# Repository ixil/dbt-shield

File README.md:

# dbt-shield
Shield: Pellet extrusion controller for ABB robotic arms w/ profinet I/O

Mini-shield: Filament extrusion controller for UR arms, to be used in the MAS ETH DFAB

## Shield
---

### Specs
---
16bit 24V digital Input\
8bit 24v digital Output\
4bit 0-10v analog Input\
4x 500mW MOSFETS\
4x SSR 240VAC 2A\
2x K-Type Thermocouple amplifiers

## Mini-Shield

### Specs
---
4bit 24V digital Input\
2x TMC2130 Stepper Driver\
2x 100W MOSFETS\
3x 500mW MOSFETS\
1x 104NT thermistor

[Pin-Out / Set-Up / Connections](https://github.com/hiiragii/dbt-shield/tree/master/mini)

### UR5 FDM  

UR 5 e3d Titan Aero + Super Volcano mounting bracket
[stl / step files](https://github.com/hiiragii/dbt-shield/tree/master/ur5aero)

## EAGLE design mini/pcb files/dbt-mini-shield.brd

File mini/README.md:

## Pinout
---

The 2x16 pin terminal blocks on the right side are directly connected to the respective arduino pin (eg D0 on the terminal block is digital pin 0 on the arduino).

## Connections
---
+ Connect the 24v power supply wires to the top terminal.
+ Connect the Extruder optional object fan to OUT0 and OUT1.
+ Connect the thermistor leads to TH0+ and TH0-, polarity doesn't matter.
+ Connect the super-volcano heater to OUT3 and GND (first 2 pins on the terminal block).
+ Connect the first stepper coil to M1.1A and M1.1B. Connect the second coil to M1.2A and M1.2B. Polarity doesn't matter, you can reverse the direction of rotation directly in software or by swapping 2 leads of the same coil (eg. M1.1A and M1.1B).  
+ Connect the 5 lead cable to the 4-bit input terminal block, where IN.b3 is the MSB.

## Set-up
---

## Digital-Input

In.b0 = heater enable, active LOW
In.b1 = stepper enable, active LOW
In.b2 = speed 
In.b3 = speed 

speed(5mm/s)  01
speed(15mm/s) 10
speed(30mm/s) 11

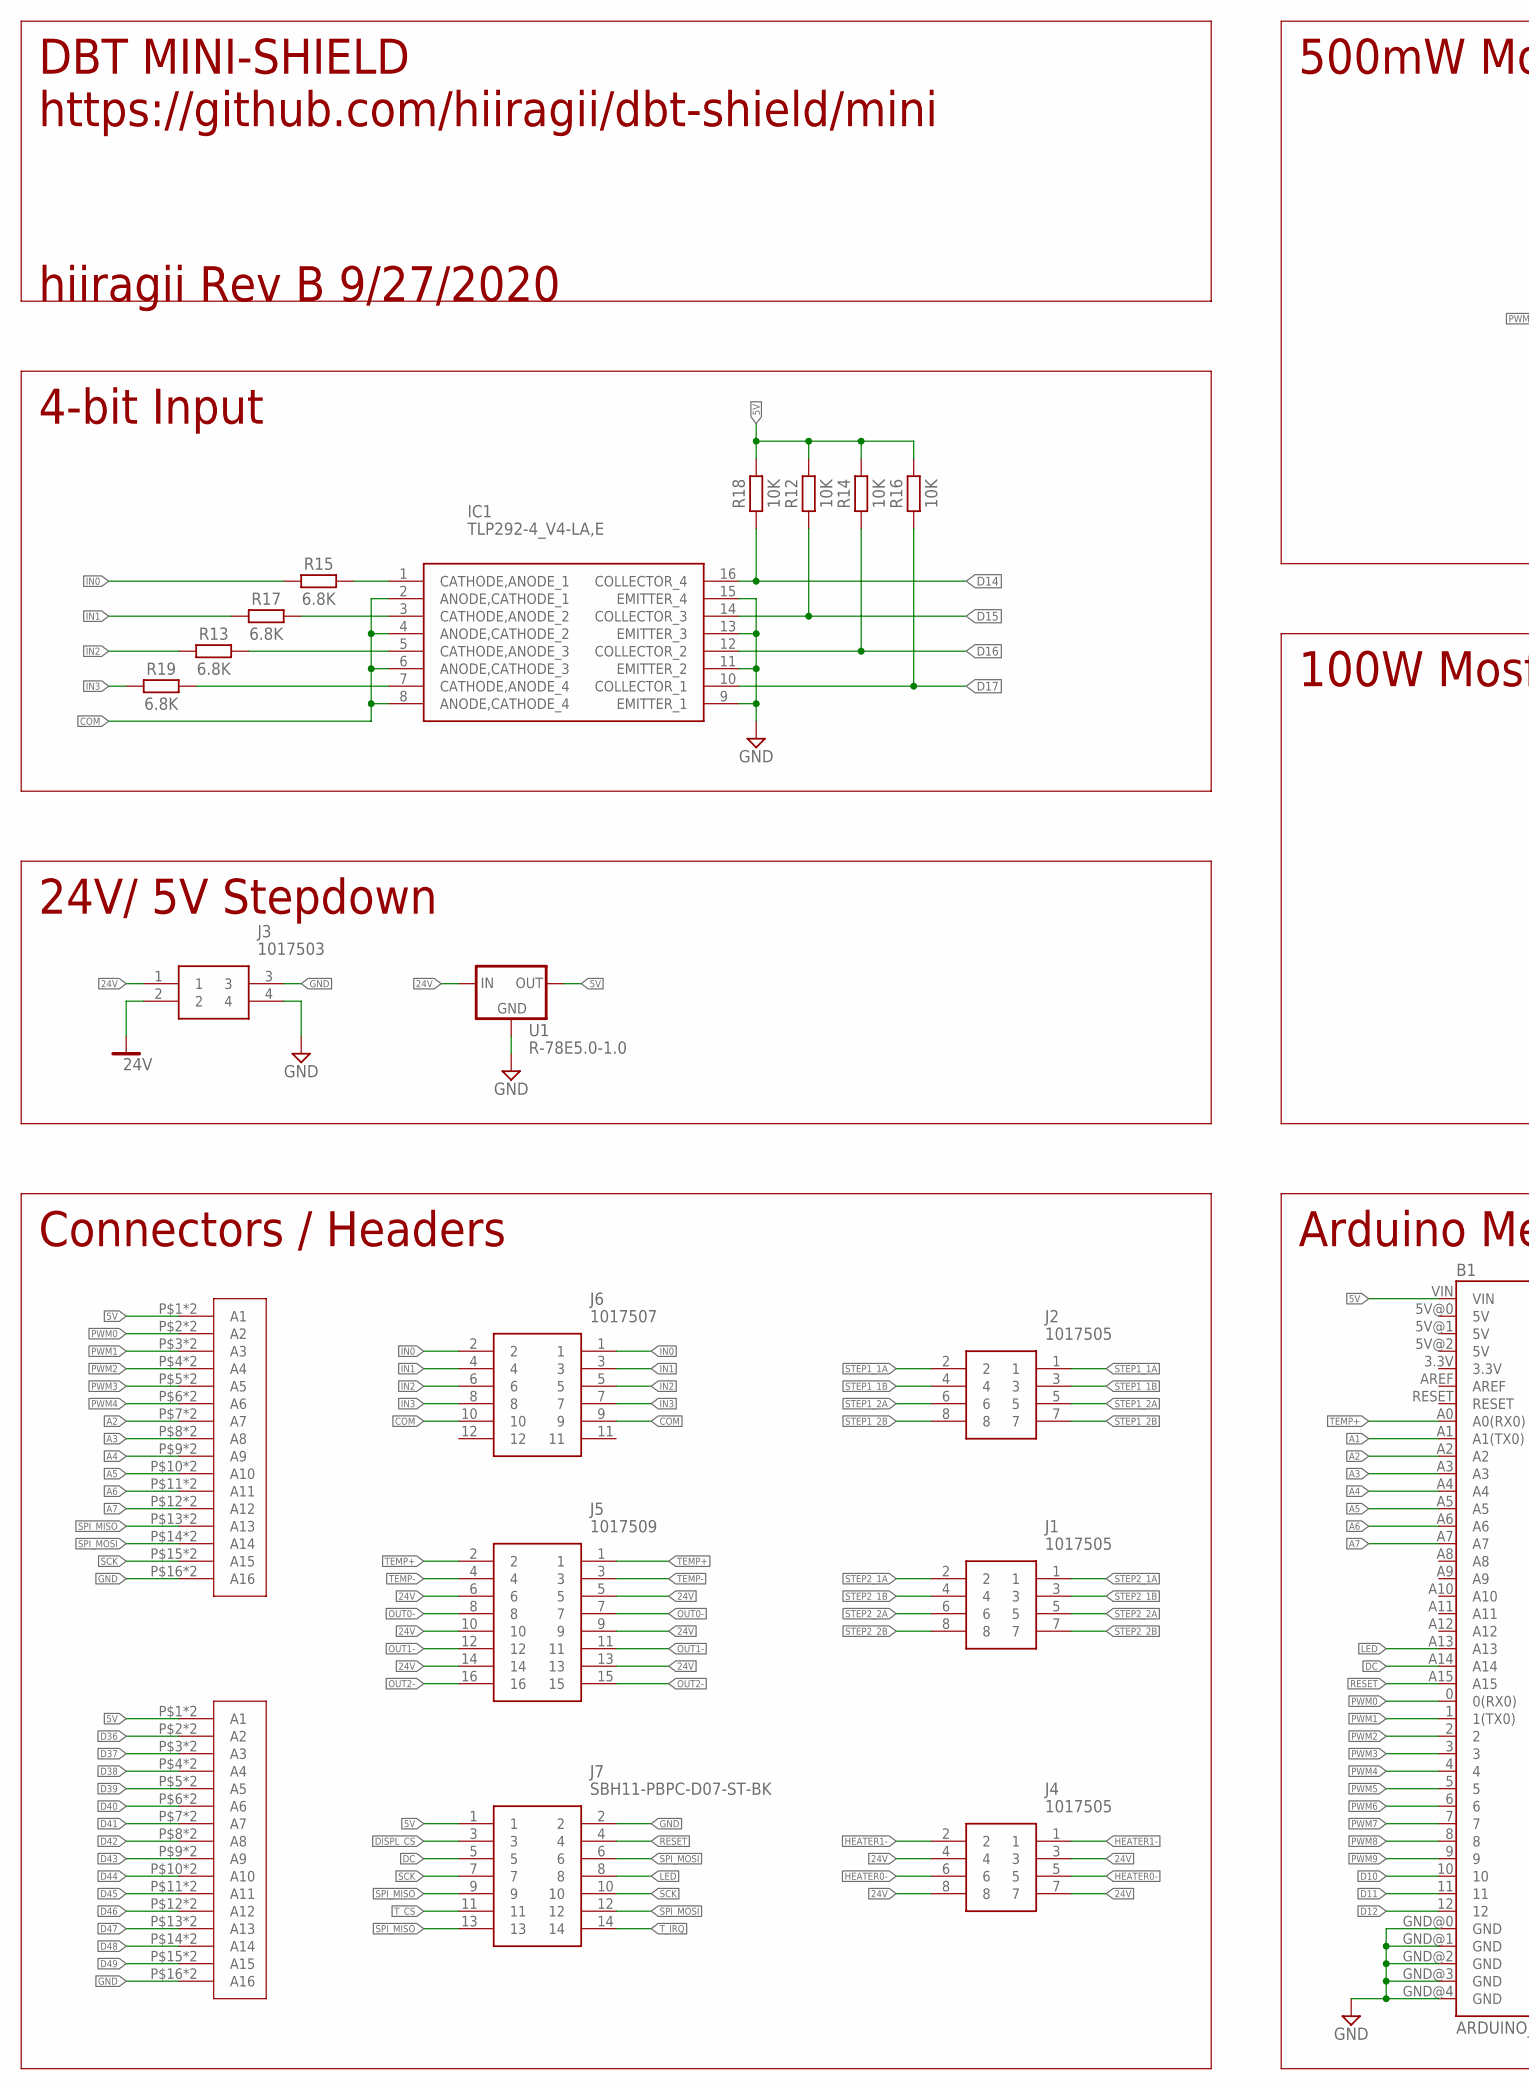
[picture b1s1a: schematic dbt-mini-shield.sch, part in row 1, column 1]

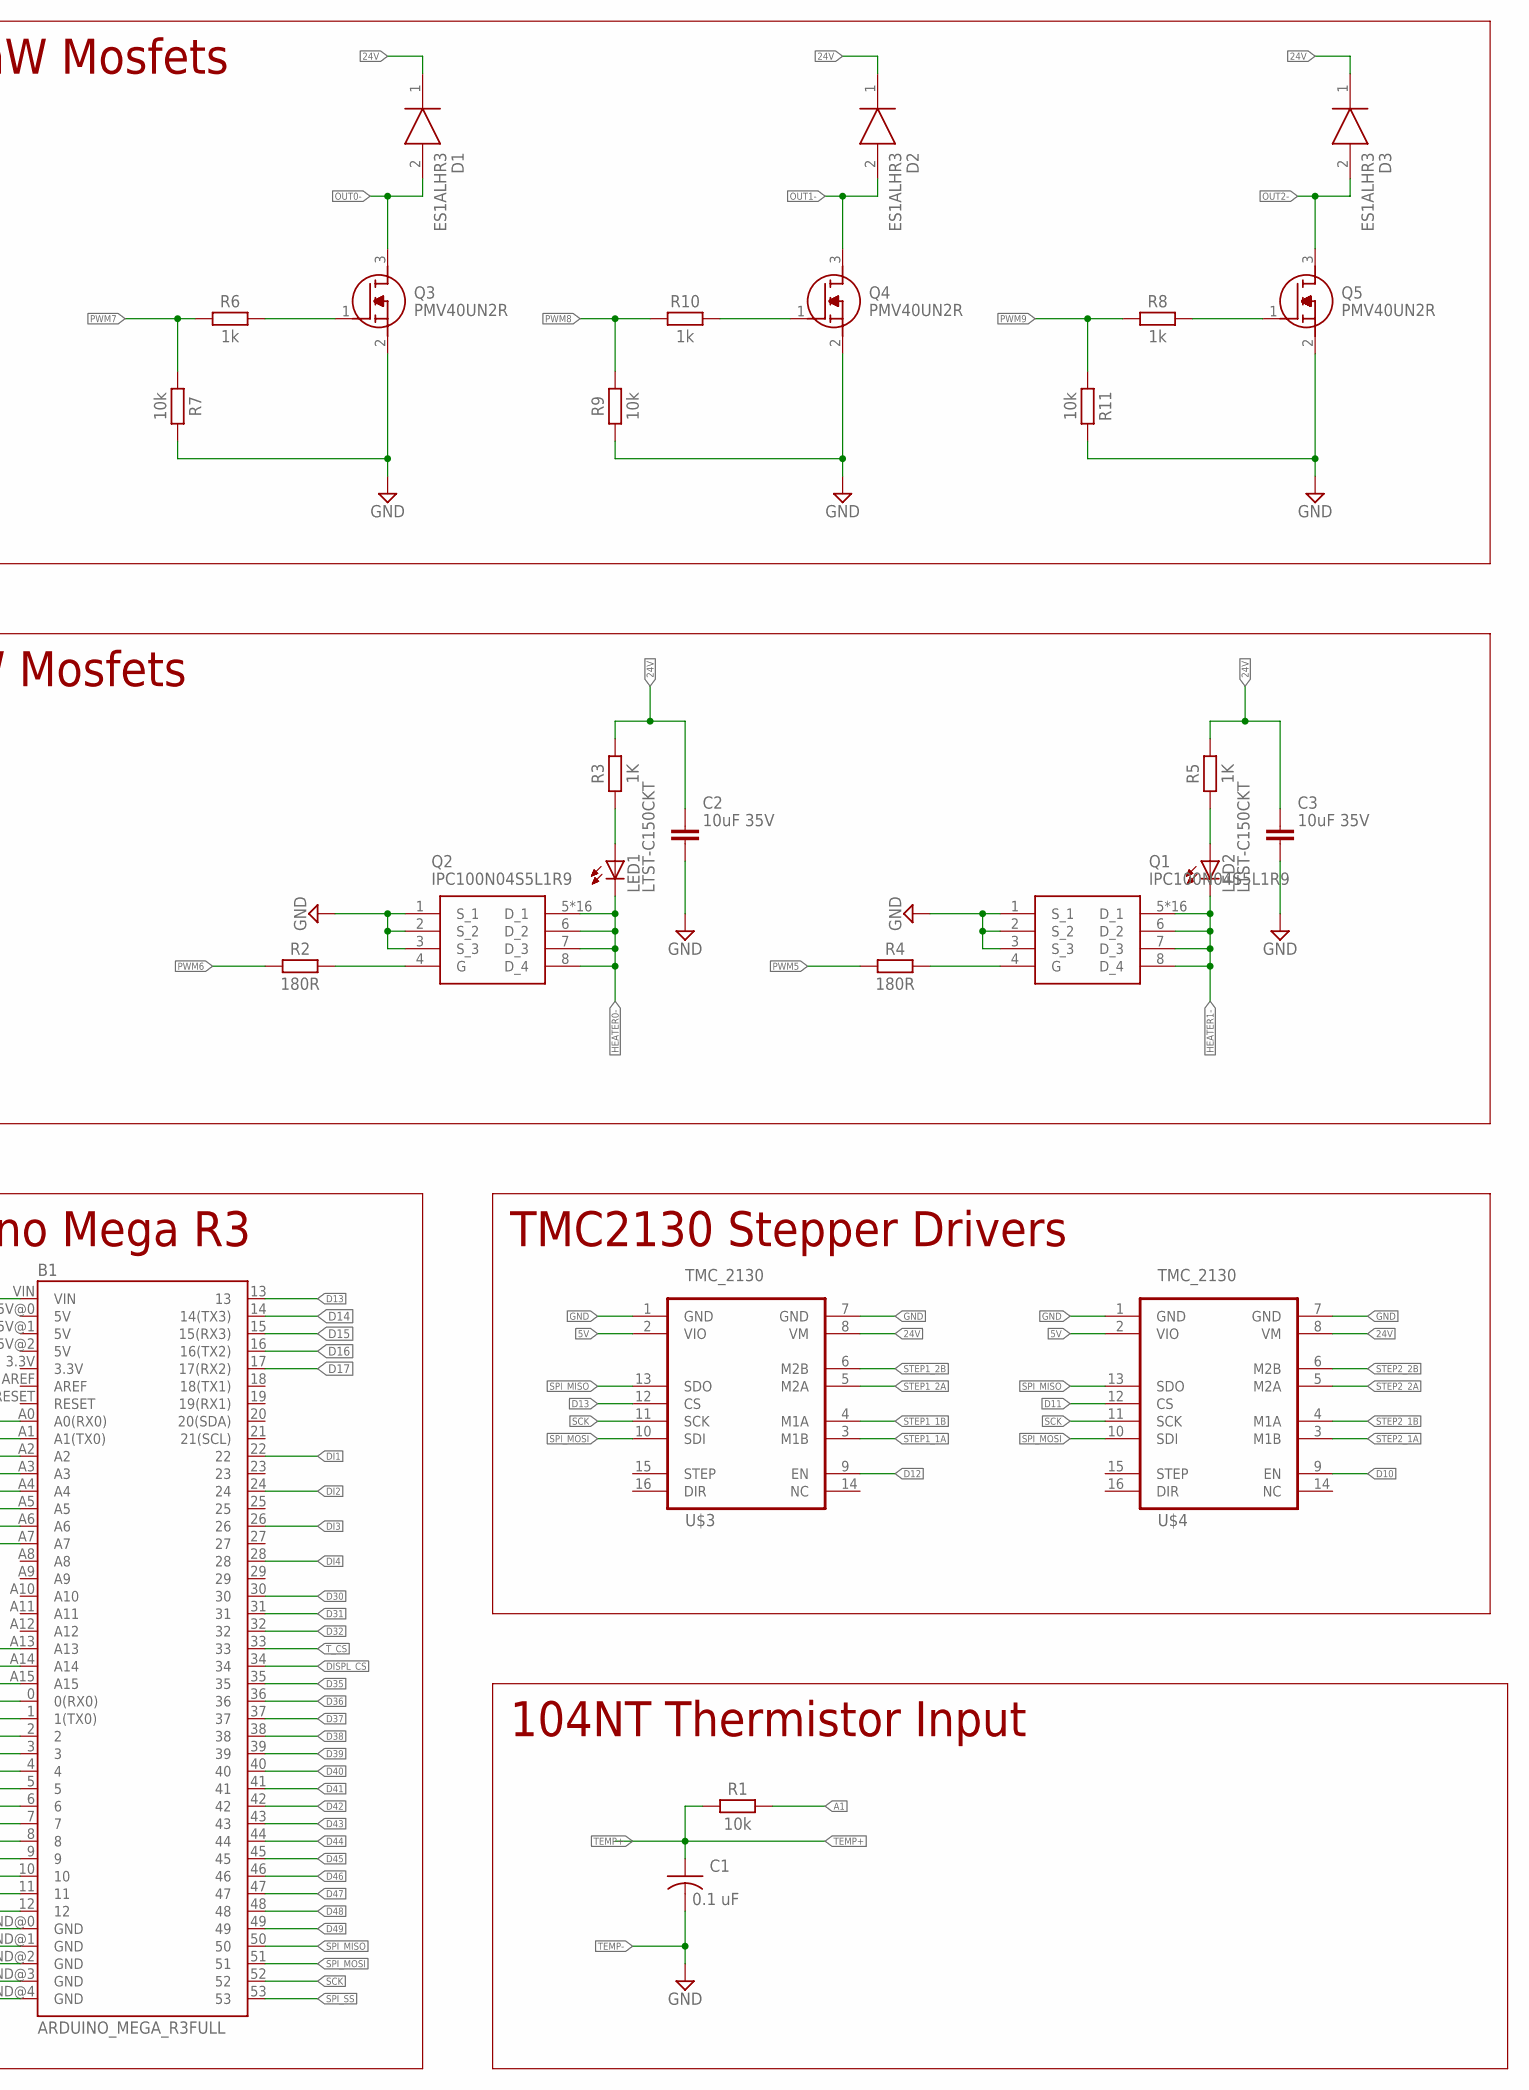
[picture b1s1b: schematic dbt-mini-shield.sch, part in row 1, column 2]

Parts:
B1: ARDUINO_MEGA_R3FULL; ARDUINO_MEGA
C1: 0.1 uF; C1206
C2, C3: 10uF 35V; CAPC3216X135
D1, D2, D3: ES1ALHR3; SODFL3618X143N
IC1: TLP292-4_V4-LA,E; SOIC127P700X230-16N
J1, J2, J4: 1017505
J3: 1017503
J5: 1017509
J6: 1017507
J7: SBH11-PBPC-D07-ST-BK; SHDR14W64P254_2X7_2528X910X910
LED1, LED2: LTST-C150CKT; CHIPLED_1206
Q1, Q2: IPC100N04S5L1R9; PG-TDSON-8
Q3, Q4, Q5: PMV40UN2R; SOT95P230X110-3N
R1, R7, R9, R11: 10k; RESC3216X70
R2, R4: 180R; RESC3216X70
R3, R5: 1K; RESC3216X70
R6, R8, R10: 1k; RESC3216X70
R12, R14, R16, R18: 10K; RESC3216X70
R13, R15, R17, R19: 6.8K; RESC3216X70
U1: R-78E5.0-1.0; DC-DC_CONVERTER_78XX
U$1, U$2: 1861991
U$3, U$4: TMC_2130

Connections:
5V: B1.VIN, J7.1, R12.2, R14.2, R16.2, R18.2, U1.VOUT (OUT), U$1.P$1 (A1), U$1.P$17 (A1), U$2.P$1 (A1), U$2.P$17 (A1), U$3.2 (VIO), U$4.2 (VIO)
24V: C2.1, C3.1, D1.1 (K), D2.1 (K), D3.1 (K), J3.1, J3.2, J4.3, J4.4, J4.7, J4.8, J5.5, J5.6, J5.9, J5.10, J5.13, J5.14, R3.2, R5.2, U1.VIN (IN), U$3.8 (VM), U$4.8 (VM)
A1: B1.A1 (A1(TX0)), R1.2
A2: B1.A2, U$1.P$7 (A7), U$1.P$23 (A7)
A3: B1.A3, U$1.P$8 (A8), U$1.P$24 (A8)
A4: B1.A4, U$1.P$9 (A9), U$1.P$25 (A9)
A5: B1.A5, U$1.P$10 (A10), U$1.P$26 (A10)
A6: B1.A6, U$1.P$11 (A11), U$1.P$27 (A11)
A7: B1.A7, U$1.P$12 (A12), U$1.P$28 (A12)
COM: IC1.2 (ANODE,CATHODE_1), IC1.4 (ANODE,CATHODE_2), IC1.6 (ANODE,CATHODE_3), IC1.8 (ANODE,CATHODE_4), J6.9, J6.10
D10: B1.10, U$4.9 (EN)
D11: B1.11, U$4.12 (CS)
D12: B1.12, U$3.9 (EN)
D13: B1.13, U$3.12 (CS)
D14: B1.14 (14(TX3)), IC1.16 (COLLECTOR_4), R18.1
D15: B1.15 (15(RX3)), IC1.14 (COLLECTOR_3), R12.1
D16: B1.16 (16(TX2)), IC1.12 (COLLECTOR_2), R14.1
D17: B1.17 (17(RX2)), IC1.10 (COLLECTOR_1), R16.1
D30: B1.30
D31: B1.31
D32: B1.32
D35: B1.35
D36: B1.36, U$2.P$2 (A2), U$2.P$18 (A2)
D37: B1.37, U$2.P$3 (A3), U$2.P$19 (A3)
D38: B1.38, U$2.P$4 (A4), U$2.P$20 (A4)
D39: B1.39, U$2.P$5 (A5), U$2.P$21 (A5)
D40: B1.40, U$2.P$6 (A6), U$2.P$22 (A6)
D41: B1.41, U$2.P$7 (A7), U$2.P$23 (A7)
D42: B1.42, U$2.P$8 (A8), U$2.P$24 (A8)
D43: B1.43, U$2.P$9 (A9), U$2.P$25 (A9)
D44: B1.44, U$2.P$10 (A10), U$2.P$26 (A10)
D45: B1.45, U$2.P$11 (A11), U$2.P$27 (A11)
D46: B1.46, U$2.P$12 (A12), U$2.P$28 (A12)
D47: B1.47, U$2.P$13 (A13), U$2.P$29 (A13)
D48: B1.48, U$2.P$14 (A14), U$2.P$30 (A14)
D49: B1.49, U$2.P$15 (A15), U$2.P$31 (A15)
DC: B1.A14, J7.5
DI1: B1.22
DI2: B1.24
DI3: B1.26
DI4: B1.28
DISPL_CS: B1.34, J7.3
G: Q2.4 (G), R2.2
G1: Q1.4 (G), R4.2
GND: B1.GND@0 (GND), B1.GND@1 (GND), B1.GND@2 (GND), B1.GND@3 (GND), B1.GND@4 (GND), C2.2, C3.2, IC1.9 (EMITTER_1), IC1.11 (EMITTER_2), IC1.13 (EMITTER_3), IC1.15 (EMITTER_4), J3.3, J3.4, J7.2, Q1.1 (S_1), Q1.2 (S_2), Q1.3 (S_3), Q2.1 (S_1), Q2.2 (S_2), Q2.3 (S_3), Q3.2 (S), Q4.2 (S), Q5.2 (S), R7.2, R9.1, R11.2, U1.GND, U$1.P$16 (A16), U$1.P$32 (A16), U$2.P$16 (A16), U$2.P$32 (A16), U$3.1 (GND), U$3.7 (GND), U$4.1 (GND), U$4.7 (GND)
HEATER0-: J4.5, J4.6, LED1.C, Q2.5 (D_1), Q2.6 (D_2), Q2.7 (D_3), Q2.8 (D_4), Q2.9 (D_1), Q2.P$1 (D_1), Q2.P$2 (D_1), Q2.P$3 (D_1), Q2.P$4 (D_1), Q2.P$5 (D_1), Q2.P$6 (D_1), Q2.P$7 (D_1), Q2.P$8 (D_1), Q2.P$9 (D_1), Q2.P$10 (D_1), Q2.P$11 (D_1), Q2.P$12 (D_1), Q2.P$13 (D_1), Q2.P$14 (D_1)
HEATER1-: J4.1, J4.2, LED2.C, Q1.5 (D_1), Q1.6 (D_2), Q1.7 (D_3), Q1.8 (D_4), Q1.9 (D_1), Q1.P$1 (D_1), Q1.P$2 (D_1), Q1.P$3 (D_1), Q1.P$4 (D_1), Q1.P$5 (D_1), Q1.P$6 (D_1), Q1.P$7 (D_1), Q1.P$8 (D_1), Q1.P$9 (D_1), Q1.P$10 (D_1), Q1.P$11 (D_1), Q1.P$12 (D_1), Q1.P$13 (D_1), Q1.P$14 (D_1)
IN0: J6.1, J6.2, R15.1
IN1: J6.3, J6.4, R17.1
IN2: J6.5, J6.6, R13.1
IN3: J6.7, J6.8, R19.1
LED: B1.A13, J7.8
unnamed: LED1.A, R3.1
unnamed: LED2.A, R5.1
unnamed: IC1.1 (CATHODE,ANODE_1), R15.2
unnamed: IC1.3 (CATHODE,ANODE_2), R17.2
unnamed: IC1.5 (CATHODE,ANODE_3), R13.2
unnamed: IC1.7 (CATHODE,ANODE_4), R19.2
unnamed: Q3.1 (G), R6.2
unnamed: Q4.1 (G), R10.2
unnamed: Q5.1 (G), R8.2
NC: U$3.14 (NC), U$4.14 (NC)
OUT0-: D1.2 (A), J5.7, J5.8, Q3.3 (D)
OUT1-: D2.2 (A), J5.11, J5.12, Q4.3 (D)
OUT2-: D3.2 (A), J5.15, J5.16, Q5.3 (D)
PWM0: B1.0 (0(RX0)), U$1.P$2 (A2), U$1.P$18 (A2)
PWM1: B1.1 (1(TX0)), U$1.P$3 (A3), U$1.P$19 (A3)
PWM2: B1.2, U$1.P$4 (A4), U$1.P$20 (A4)
PWM3: B1.3, U$1.P$5 (A5), U$1.P$21 (A5)
PWM4: B1.4, U$1.P$6 (A6), U$1.P$22 (A6)
PWM5: B1.5, R4.1
PWM6: B1.6, R2.1
PWM7: B1.7, R6.1, R7.1
PWM8: B1.8, R9.2, R10.1
PWM9: B1.9, R8.1, R11.1
RESET: B1.A15, J7.4
SCK: B1.52, J7.7, J7.10, U$1.P$15 (A15), U$1.P$31 (A15), U$3.11 (SCK), U$4.11 (SCK)
SPI_MISO: B1.50, J7.9, J7.13, U$1.P$13 (A13), U$1.P$29 (A13), U$3.13 (SDO), U$4.13 (SDO)
SPI_MOSI: B1.51, J7.6, J7.12, U$1.P$14 (A14), U$1.P$30 (A14), U$3.10 (SDI), U$4.10 (SDI)
SPI_SS: B1.53
STEP1_1A: J2.1, J2.2, U$3.3 (M1B)
STEP1_1B: J2.3, J2.4, U$3.4 (M1A)
STEP1_2A: J2.5, J2.6, U$3.5 (M2A)
STEP1_2B: J2.7, J2.8, U$3.6 (M2B)
STEP2_1A: J1.1, J1.2, U$4.3 (M1B)
STEP2_1B: J1.3, J1.4, U$4.4 (M1A)
STEP2_2A: J1.5, J1.6, U$4.5 (M2A)
STEP2_2B: J1.7, J1.8, U$4.6 (M2B)
TEMP+: B1.A0 (A0(RX0)), C1.1, J5.1, J5.2, R1.1
TEMP-: C1.2, J5.3, J5.4
T_CS: B1.33, J7.11
T_IRQ: J7.14

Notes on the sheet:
DBT MINI-SHIELD https://github.com/hiiragii/dbt-shield/mini
hiiragii Rev B 9/27/2020
4-bit Input
24V/ 5V Stepdown
Connectors / Headers
100W Mosfets
500mW Mosfets
Arduino Mega R3
TMC2130 Stepper Drivers
104NT Thermistor Input

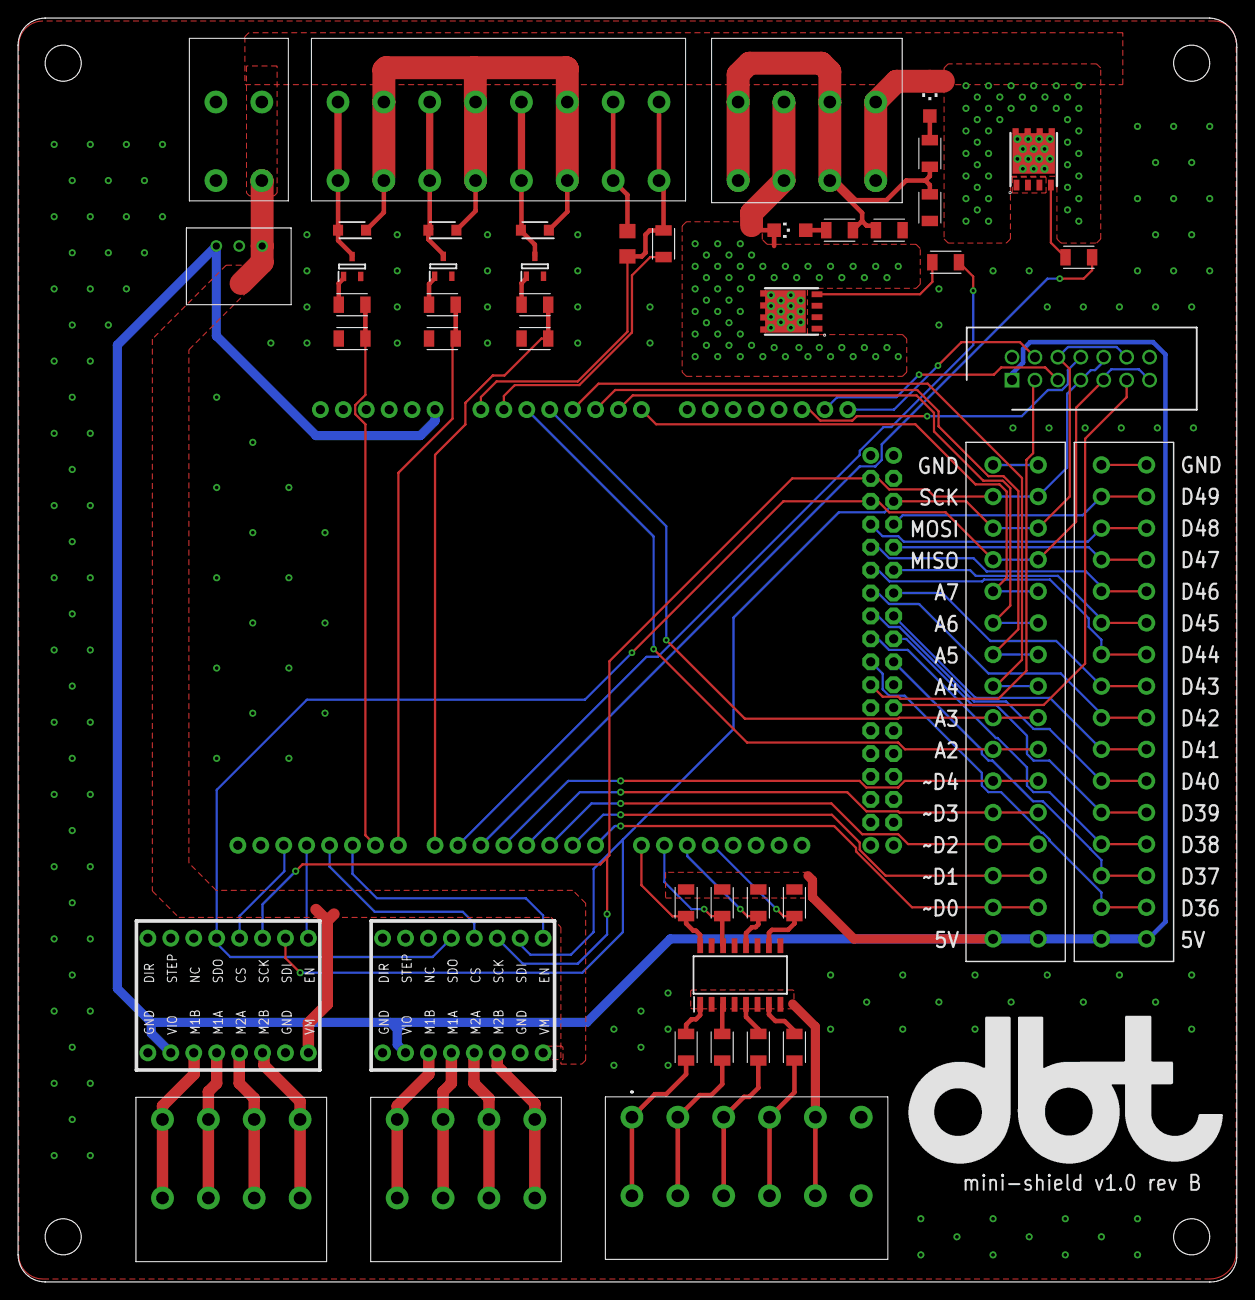
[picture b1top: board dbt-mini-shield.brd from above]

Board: 2 copper layers, 135.0 x 140.0 mm, 46 parts (1 on the bottom side), 82 nets.

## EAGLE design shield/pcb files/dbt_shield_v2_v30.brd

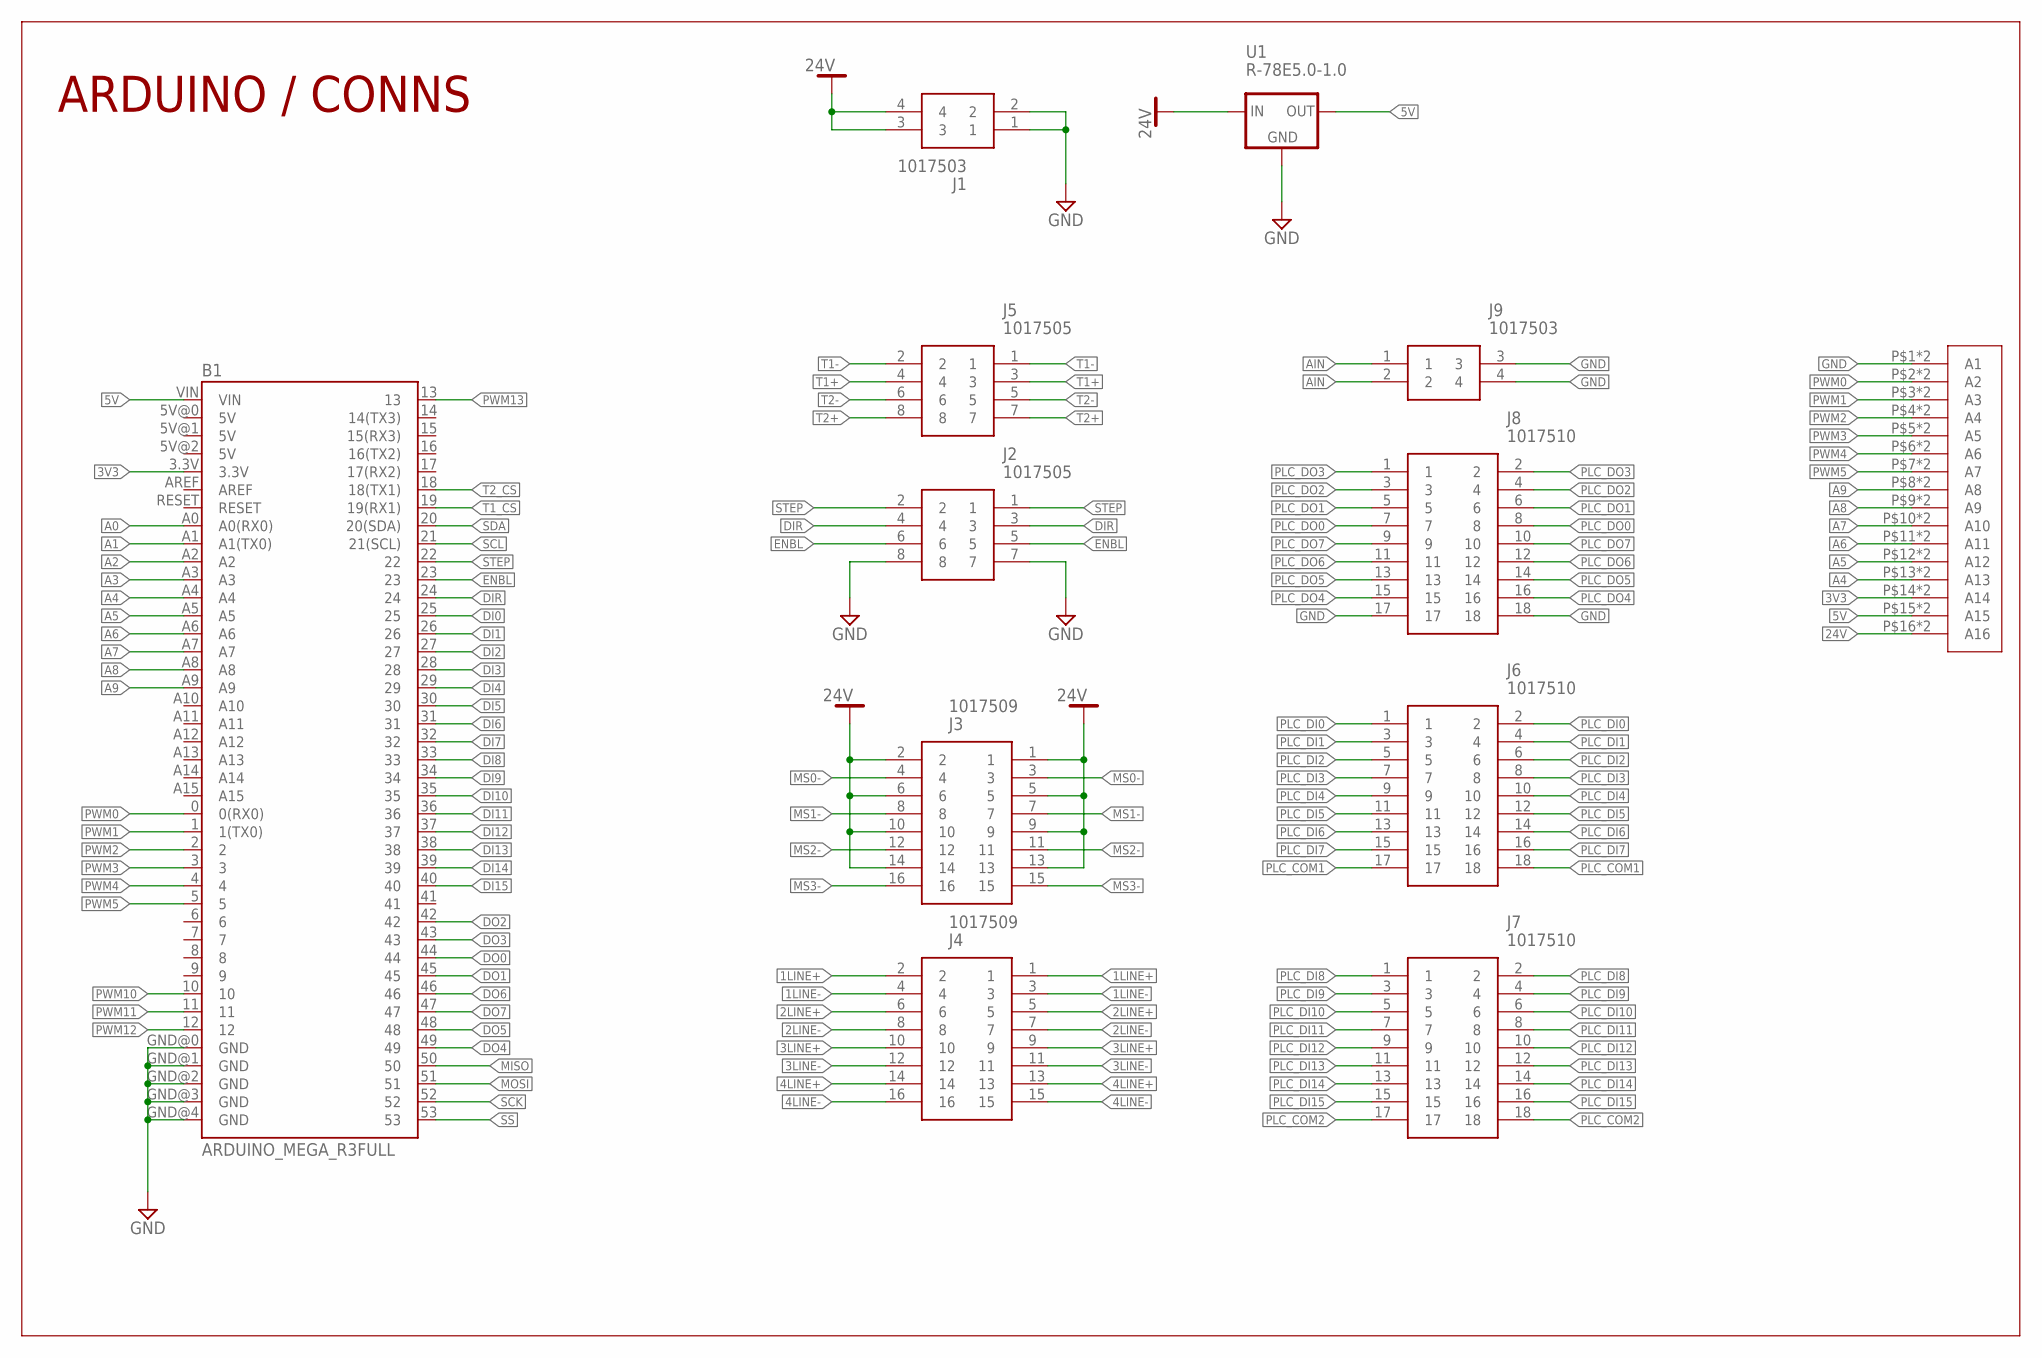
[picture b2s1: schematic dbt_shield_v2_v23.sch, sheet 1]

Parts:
B1: ARDUINO_MEGA_R3FULL; ARDUINO_MEGA
J1, J9: 1017503
J2, J5: 1017505
J3, J4: 1017509
J6, J7, J8: 1017510; SHDR18W120P870X508_2X9_4652X18
U1: R-78E5.0-1.0; DC-DC_CONVERTER_78XX
U$1: 1861991

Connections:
1LINE+: J4.1, J4.2; also elsewhere on the board
1LINE-: J4.3, J4.4; also elsewhere on the board
2LINE+: J4.5, J4.6; also elsewhere on the board
2LINE-: J4.7, J4.8; also elsewhere on the board
3LINE+: J4.9, J4.10; also elsewhere on the board
3LINE-: J4.11, J4.12; also elsewhere on the board
3V3: B1.3.3V, U$1.P$14 (A14), U$1.P$30 (A14); also elsewhere on the board
4LINE+: J4.13, J4.14; also elsewhere on the board
4LINE-: J4.15, J4.16; also elsewhere on the board
5V: B1.VIN, U1.VOUT (OUT), U$1.P$15 (A15), U$1.P$31 (A15); also elsewhere on the board
24V: J1.3, J1.4, J3.1, J3.2, J3.5, J3.6, J3.9, J3.10, J3.13, J3.14, U1.VIN (IN), U$1.P$16 (A16), U$1.P$32 (A16); also elsewhere on the board
A0: B1.A0 (A0(RX0)); also elsewhere on the board
A1: B1.A1 (A1(TX0)); also elsewhere on the board
A2: B1.A2; also elsewhere on the board
A3: B1.A3; also elsewhere on the board
A4: B1.A4, U$1.P$13 (A13), U$1.P$29 (A13)
A5: B1.A5, U$1.P$12 (A12), U$1.P$28 (A12)
A6: B1.A6, U$1.P$11 (A11), U$1.P$27 (A11)
A7: B1.A7, U$1.P$10 (A10), U$1.P$26 (A10)
A8: B1.A8, U$1.P$9 (A9), U$1.P$25 (A9)
A9: B1.A9, U$1.P$8 (A8), U$1.P$24 (A8)
AIN: J9.1, J9.2; also elsewhere on the board
DI0: B1.25; also elsewhere on the board
DI1: B1.26; also elsewhere on the board
DI2: B1.27; also elsewhere on the board
DI3: B1.28; also elsewhere on the board
DI4: B1.29; also elsewhere on the board
DI5: B1.30; also elsewhere on the board
DI6: B1.31; also elsewhere on the board
DI7: B1.32; also elsewhere on the board
DI8: B1.33; also elsewhere on the board
DI9: B1.34; also elsewhere on the board
DI10: B1.35; also elsewhere on the board
DI11: B1.36; also elsewhere on the board
DI12: B1.37; also elsewhere on the board
DI13: B1.38; also elsewhere on the board
DI14: B1.39; also elsewhere on the board
DI15: B1.40; also elsewhere on the board
DIR: B1.24, J2.3, J2.4
DO0: B1.44; also elsewhere on the board
DO1: B1.45; also elsewhere on the board
DO2: B1.42; also elsewhere on the board
DO3: B1.43; also elsewhere on the board
DO4: B1.49; also elsewhere on the board
DO5: B1.48; also elsewhere on the board
DO6: B1.46; also elsewhere on the board
DO7: B1.47; also elsewhere on the board
ENBL: B1.23, J2.5, J2.6
GND: B1.GND@0 (GND), B1.GND@1 (GND), B1.GND@2 (GND), B1.GND@3 (GND), B1.GND@4 (GND), J1.1, J1.2, J2.7, J2.8, J8.17, J8.18, J9.3, J9.4, U1.GND, U$1.P$1 (A1), U$1.P$17 (A1); also elsewhere on the board
MISO: B1.50; also elsewhere on the board
MOSI: B1.51
MS0-: J3.3, J3.4; also elsewhere on the board
MS1-: J3.7, J3.8; also elsewhere on the board
MS2-: J3.11, J3.12; also elsewhere on the board
MS3-: J3.15, J3.16; also elsewhere on the board
PLC_COM1: J6.17, J6.18; also elsewhere on the board
PLC_COM2: J7.17, J7.18; also elsewhere on the board
PLC_DI0: J6.1, J6.2; also elsewhere on the board
PLC_DI1: J6.3, J6.4; also elsewhere on the board
PLC_DI2: J6.5, J6.6; also elsewhere on the board
PLC_DI3: J6.7, J6.8; also elsewhere on the board
PLC_DI4: J6.9, J6.10; also elsewhere on the board
PLC_DI5: J6.11, J6.12; also elsewhere on the board
PLC_DI6: J6.13, J6.14; also elsewhere on the board
PLC_DI7: J6.15, J6.16; also elsewhere on the board
PLC_DI8: J7.1, J7.2; also elsewhere on the board
PLC_DI9: J7.3, J7.4; also elsewhere on the board
PLC_DI10: J7.5, J7.6; also elsewhere on the board
PLC_DI11: J7.7, J7.8; also elsewhere on the board
PLC_DI12: J7.9, J7.10; also elsewhere on the board
PLC_DI13: J7.11, J7.12; also elsewhere on the board
PLC_DI14: J7.13, J7.14; also elsewhere on the board
PLC_DI15: J7.15, J7.16; also elsewhere on the board
PLC_DO0: J8.7, J8.8; also elsewhere on the board
PLC_DO1: J8.5, J8.6; also elsewhere on the board
PLC_DO2: J8.3, J8.4; also elsewhere on the board
PLC_DO3: J8.1, J8.2; also elsewhere on the board
PLC_DO4: J8.15, J8.16; also elsewhere on the board
PLC_DO5: J8.13, J8.14; also elsewhere on the board
PLC_DO6: J8.11, J8.12; also elsewhere on the board
PLC_DO7: J8.9, J8.10; also elsewhere on the board
PWM0: B1.0 (0(RX0)), U$1.P$2 (A2), U$1.P$18 (A2)
PWM1: B1.1 (1(TX0)), U$1.P$3 (A3), U$1.P$19 (A3)
PWM2: B1.2, U$1.P$4 (A4), U$1.P$20 (A4)
PWM3: B1.3, U$1.P$5 (A5), U$1.P$21 (A5)
PWM4: B1.4, U$1.P$6 (A6), U$1.P$22 (A6)
PWM5: B1.5, U$1.P$7 (A7), U$1.P$23 (A7)
PWM10: B1.10; also elsewhere on the board
PWM11: B1.11; also elsewhere on the board
PWM12: B1.12; also elsewhere on the board
PWM13: B1.13; also elsewhere on the board
SCK: B1.52; also elsewhere on the board
SCL: B1.21 (21(SCL)); also elsewhere on the board
SDA: B1.20 (20(SDA)); also elsewhere on the board
SS: B1.53
STEP: B1.22, J2.1, J2.2
T1+: J5.3, J5.4; also elsewhere on the board
T1-: J5.1, J5.2; also elsewhere on the board
T1_CS: B1.19 (19(RX1)); also elsewhere on the board
T2+: J5.7, J5.8; also elsewhere on the board
T2-: J5.5, J5.6; also elsewhere on the board
T2_CS: B1.18 (18(TX1)); also elsewhere on the board

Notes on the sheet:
ARDUINO / CONNS

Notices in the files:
parts and their libraries:
SparkFun-Aesthetics: Licensing: CC v3.0 Share-Alike You are welcome to use this library for commercial purposes.
SparkFun-AnalogIC: Licensing:Creative Commons ShareAlike 4.0 International - https://creativecommons.org/licenses/by-sa/4.0
